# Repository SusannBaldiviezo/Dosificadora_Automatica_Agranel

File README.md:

# Dosificadora_Automatica_Agranel
El proyecto consiste en el diseño e implementación de una dosificadora automática de granos controlada mediante Arduino

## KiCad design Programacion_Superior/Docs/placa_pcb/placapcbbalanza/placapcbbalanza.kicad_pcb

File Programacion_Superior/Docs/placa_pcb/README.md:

# 🧩 Proyecto PCB - Diseño y Fabricación

Este documento explica el proceso de diseño y fabricación de una **placa de circuito impreso (PCB)** realizada manualmente, desde el diseño esquemático hasta el montaje final. El objetivo fue crear una placa funcional a partir de un circuito previamente diseñado en software de simulación electrónica.

---

## 🧰 Herramientas y materiales utilizados

- Software: [KiCad](https://kicad.org/) (también se puede usar Proteus, EasyEDA, etc.)
- Impresora láser
- Papel transfer
- Placa virgen de cobre
- Alcohol isopropílico
- Plancha o laminadora
- Ácido férrico
- Micrómetro digital o manual
- Taladro para PCB
- Estaño y soldador
- Componentes electrónicos (resistencias, capacitores, Arduino, etc.)

---

## 📝 Pasos realizados

### 1. Diseño del esquema eléctrico
Se utilizó **KiCad** para crear el esquema del circuito, seleccionando y conectando los componentes electrónicos de acuerdo a la lógica del sistema a implementar.

### 2. Asignación de huellas (footprints)
A cada componente del esquema se le asignó una **huella física**, que representa su forma y tamaño en la placa.  
En caso de no conocerla, se midió con un **micrómetro** para determinar dimensiones aproximadas (ej. 4 mm).  
Para el Arduino y otros módulos comunes, se usaron las huellas disponibles por defecto.

### 3. Diseño del PCB
Con las huellas asignadas, se enrutaron las pistas para unir los componentes y se organizó el diseño del PCB, cuidando el orden y evitando cruces de pistas innecesarios.

### 4. Impresión del diseño
El diseño del PCB se imprimió en **papel transfer** utilizando una **impresora láser**, en modo espejo (espejado) para que coincida al colocarlo sobre la placa.

### 5. Preparación de la placa
Se limpió la **placa virgen de cobre** con **alcohol isopropílico** para eliminar grasa o impurezas que pudieran impedir una buena transferencia.

### 6. Transferencia del diseño a la placa
Se colocó el papel transfer (con el diseño) sobre la parte de cobre de la placa.  
Se aplicó calor con una **plancha casera durante 10 minutos** para que el tóner se adhiera al cobre.

### 7. Ataque químico con ácido férrico
Se sumergió la placa en **ácido férrico** y se removió hasta que se eliminaron las partes de cobre no protegidas por el tóner.

### 8. Perforado
Una vez revelada, se perforaron los orificios necesarios con un **taladro manual o de banco**, para permitir la inserción de los componentes.

### 9. Montaje y soldadura
Finalmente, se colocaron los componentes sobre la placa y se procedió a **soldar cada uno cuidadosamente**, verificando continuidad con multímetro.

---

## ✅ Resultado final

La PCB resultante es completamente funcional y fue construida de forma artesanal, aplicando conocimientos de diseño electrónico y técnicas de fabricación casera. Esta metodología permite crear prototipos confiables sin necesidad de mandar a fabricar placas industrialmente.

---

## 🧠 Notas finales

- Se recomienda realizar pruebas del circuito en protoboard antes de fabricar la placa.
- Utilizar guantes y protección adecuada al manipular ácido férrico.
- Para diseños más complejos, se puede optar por servicios de fabricación como JLCPCB o PCBWay.

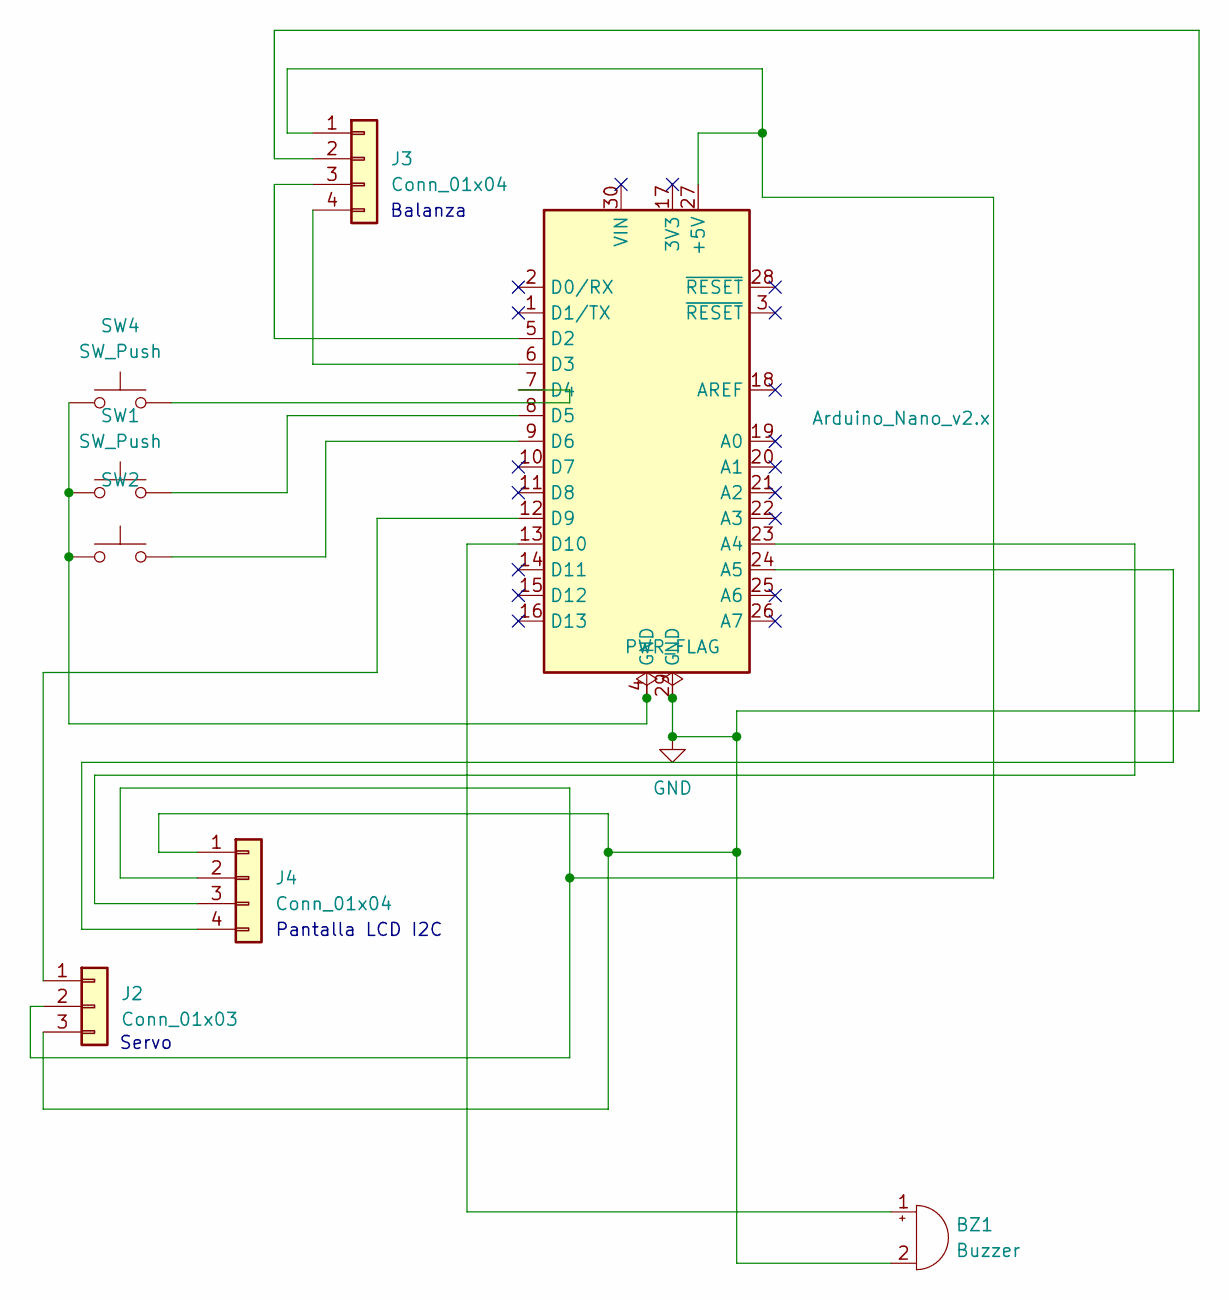
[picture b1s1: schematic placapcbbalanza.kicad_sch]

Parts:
A1: Arduino_Nano_v2.x; Arduino_Nano
BZ1: Buzzer; MagneticBuzzer_PUI_AT-0927-TT-6-R
J2: Conn_01x03; PinHeader_1x03_P2.54mm_Vertical
J3, J4: Conn_01x04; PinHeader_1x04_P2.54mm_Vertical
SW1, SW2, SW4: SW_Push; SW_PUSH_1P1T_6x3.5mm_H4.3_APEM_MJTP1243

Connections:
GND: A1.29 (GND), BZ1.2 (-), J2.3, J3.2, J4.1
unnamed: A1.27 (+5V), J2.2, J3.1, J4.2
unnamed: A1.23 (A4), J4.3
unnamed: A1.24 (A5), J4.4
unnamed: A1.5 (D2), J3.3
unnamed: A1.6 (D3), J3.4
unnamed: A1.7 (D4), SW4.2
unnamed: A1.8 (D5), SW1.2
unnamed: A1.9 (D6), SW2.2
unnamed: A1.12 (D9), J2.1
unnamed: A1.13 (D10), BZ1.1 (+)
unnamed: A1.4 (GND), SW1.1, SW2.1, SW4.1

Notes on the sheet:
Pantalla LCD I2C
Balanza
Servo

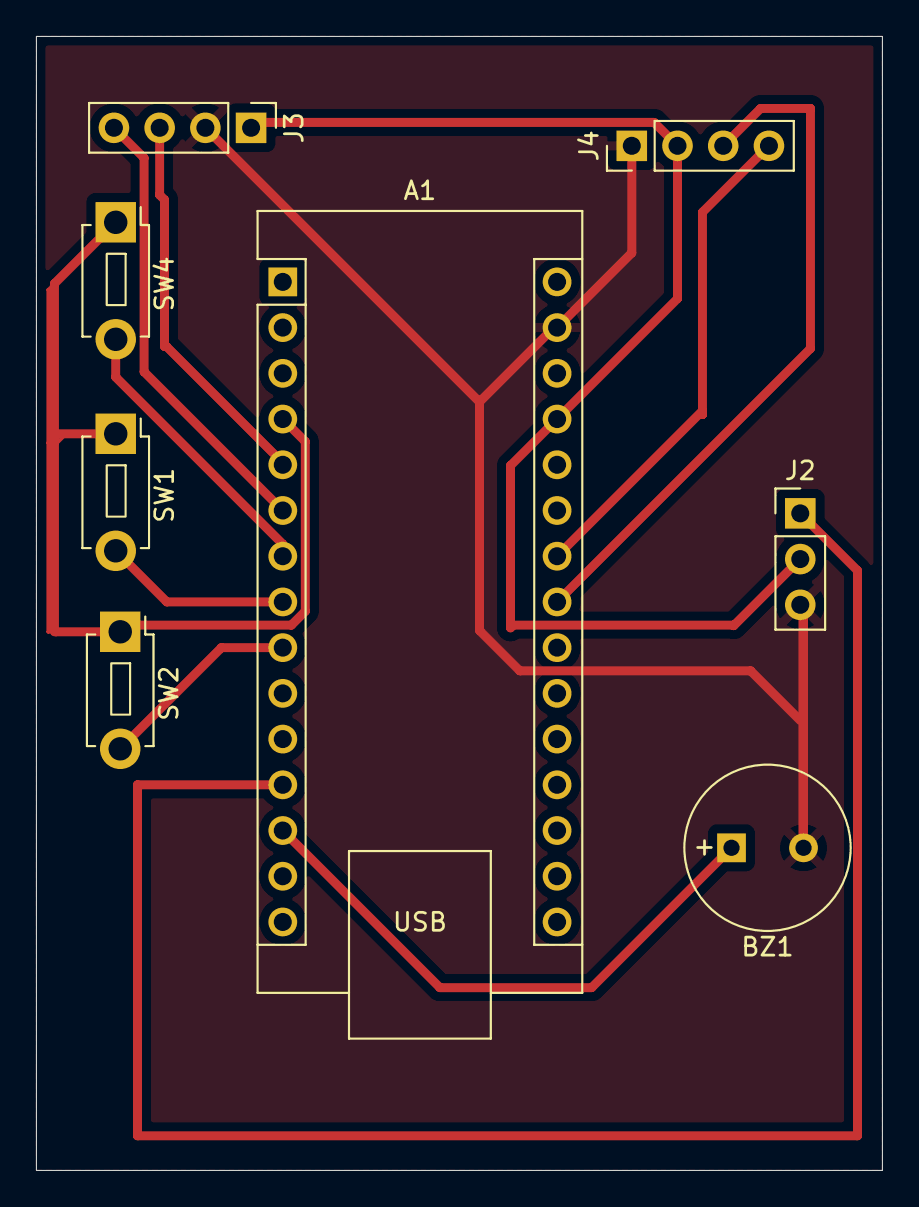
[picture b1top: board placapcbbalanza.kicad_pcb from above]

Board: 2 copper layers, 47.0 x 63.0 mm, 8 parts (0 on the bottom side), 12 nets.

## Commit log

2025-06-03 gitignore
2025-06-08 Borrador .ino de seniales
2025-06-08 Actualicé la lógica de pesaje en FFT y capturar xd
2025-06-09 Listo botones.c
2025-06-09 Listo botones.h
2025-06-09 Listo pantalla.h
2025-06-09 Listo pantalla.c
2025-06-09 Listp balanza.h
2025-06-09 Listo balanza.c
2025-06-09 Listo servos h y c
2025-06-09 Listos buzzer .c y .h
2025-06-09 me olvide el readme xd
2025-06-09 primer borrador del main, para conexion con FastAPi
2025-06-09 orden de carpetas
2025-06-09 parte del codigo de arduino
2025-06-09 organizacion de carpetas
2025-06-09 codigo
2025-06-12 creacion_de_tree_main_+_readme
2025-06-13 Planos de la pcb, pdf del plano, y archivos kicad
2025-06-13 README del funcionamiento
2025-06-13 Imagenes de datos tecnicos de la pcb
2025-06-13 Readme del funciomaniento del codigo
2025-06-13 Union de la carpeta imagenes en placapCB
2025-06-13 diagrams_
2025-06-13 codigo_para_interfaz_web_con_FastAPi_
2025-06-13 archivo de texto del arbol
2025-06-13 diapositivas_readme
2025-06-13 readme
2025-06-13 main.ino
2025-06-13 funciones.cpp
2025-06-13 funciones.h
2025-06-13 entorno virtual
2025-06-13 código para calibrar la balanza
2025-06-13 plano de AutoCad para la estructura
2025-06-13 lista de materiales
2025-06-17 análisis de señales
